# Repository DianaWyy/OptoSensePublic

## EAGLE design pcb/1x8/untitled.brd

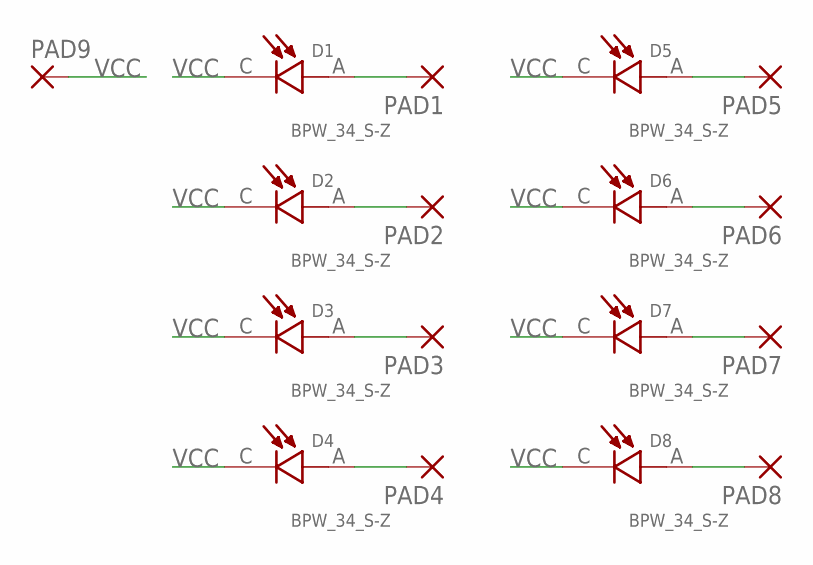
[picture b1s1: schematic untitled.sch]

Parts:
D1, D2, D3, D4, D5, D6, D7, D8: BPW_34_S-Z; DIO_BPW_34_S-Z
PAD1, PAD2, PAD3, PAD4, PAD5, PAD6, PAD7, PAD8, PAD9: SMD2; SMD1,27-2,54

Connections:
unnamed: D1.A, PAD1.1
unnamed: D2.A, PAD2.1
unnamed: D3.A, PAD3.1
unnamed: D4.A, PAD4.1
unnamed: D5.A, PAD5.1
unnamed: D6.A, PAD6.1
unnamed: D7.A, PAD7.1
unnamed: D8.A, PAD8.1
VCC: D1.C, D2.C, D3.C, D4.C, D5.C, D6.C, D7.C, D8.C, PAD9.1

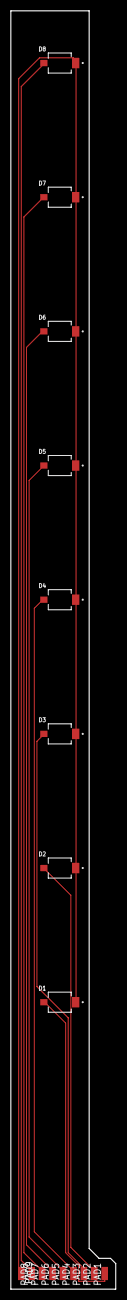
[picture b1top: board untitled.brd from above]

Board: 2 copper layers, 20.1 x 245.0 mm, 17 parts (0 on the bottom side), 9 nets.

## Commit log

2019-08-08 Added colormap and UI adjustments
2019-08-08 Added gitignore
2019-08-08 removed DS_Store
2019-08-08 added javascript code and python code that Dingtian gave me to start with
2019-08-09 Added FPS calculation, added pcb files, added pinout map
2019-08-09 Added 1pixel version visualizer, added rolling graph
2019-08-09 flipped the collor mapping (blue low light, red high light)
2019-08-09 added light threshold detection
2019-08-12 added processing codode to save light measurements into csv by pressing key 0, 1, .. 7
2019-08-13 Finished pill bottle demo with first dirivative threshold detection
2019-08-13 added step count demo code
2019-08-13 Added 16-bit js code
2019-08-19 new push from diana
2019-08-20 changed 64 pixel code to 8 pixel (16bit per pixel)
2019-08-21 Refrigerator Visualizer
2019-08-23 Added java code for liquid detection
2019-08-23 added embeded code for 8 pixels
2019-08-25 add latest code before sync with dingtian
2019-08-25 changed ble name in the javascript code to optoSense-liquid
2019-08-25 added interactive machine learning code for liquid detection
2019-08-25 added grip classification code, feature is all 8 measurements
2019-08-27 Created wristband application
2019-08-29 Refrigerator storyboard first draft
2019-08-29 Refrigerator Demo
2019-09-04 Refrigerator demo - draft2
2019-09-04 Refrigerator UI Demo -- Draft 3
2019-09-04 Pill Bottle Demo -- Draft 1
2019-09-05 Updated the c code and added writband processing code
2019-09-06 Liquid Detection Demo -- Draft 1
2019-09-07 Added 1x8 soft pcb design
2019-09-10 Added rule-based liquid detection
2019-09-11 Reorganize files
2019-09-11 Update tcp_visualizer_wristband.pde
    Included simulation for wristband
2019-09-16 Update PillBottle_UI
2019-09-18 Update Liquid_UI
2019-09-22 Add 2D (7x7) visualization and background calibration
2019-09-22 Add WristBand UI
2019-09-22 Update WristBand UI
2019-10-02 Update PillBottle
2019-10-02 Update UI colors
2019-10-08 Create UI for 2D sensor
2019-10-18 Create User Study UI
2019-10-21 add UI for 2D
2019-10-30 Update 0D UIs
2019-10-30 Update general 0D UI
2019-11-03 Create User Study UI for touch experiment
2019-11-04 Update UserUI2
2019-11-20 clean code
2019-11-20 delete
2020-12-12 Bump ini from 1.3.5 to 1.3.8 in /javascript
    Bumps [ini](https://github.com/isaacs/ini) from 1.3.5 to 1.3.8.
    - [Release notes](https://github.com/isaacs/ini/releases)
    - [Commits](https://github.com/isaacs/ini/compare/v1.3.5...v1.3.8)
